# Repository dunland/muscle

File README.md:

## folder structure

**[>>FIND THE PROJECT MANUAL HERE<<](Doc/SUPER_MUSCLE_MANUAL-0.2.0.pdf)**

```
project
└───Code
│       code folder. contains subfolders 
│	└───teensy
│	│	holding the main code
│	└───debug
│	│	for Arduino-sketches used to evaluate the contact mic sensitivities
│	└───processing
│	│	with an exemplary sketch for the real-time generation of visuals
│	└───python
│		with a script supporting the calibration process graphically
└───Doc
│       Documentation folder with images and progress logs and other media files
└───hardware
│	CAD and ECAD files
└───literature
│	some interesting material on using piezo microphones, interrupts on teensy, etc
└───logs
│	this folder holds logs that are recorded from contact microphone streams
│	while playing the instruments
└───misc
	miscellaneous.
```

## project management

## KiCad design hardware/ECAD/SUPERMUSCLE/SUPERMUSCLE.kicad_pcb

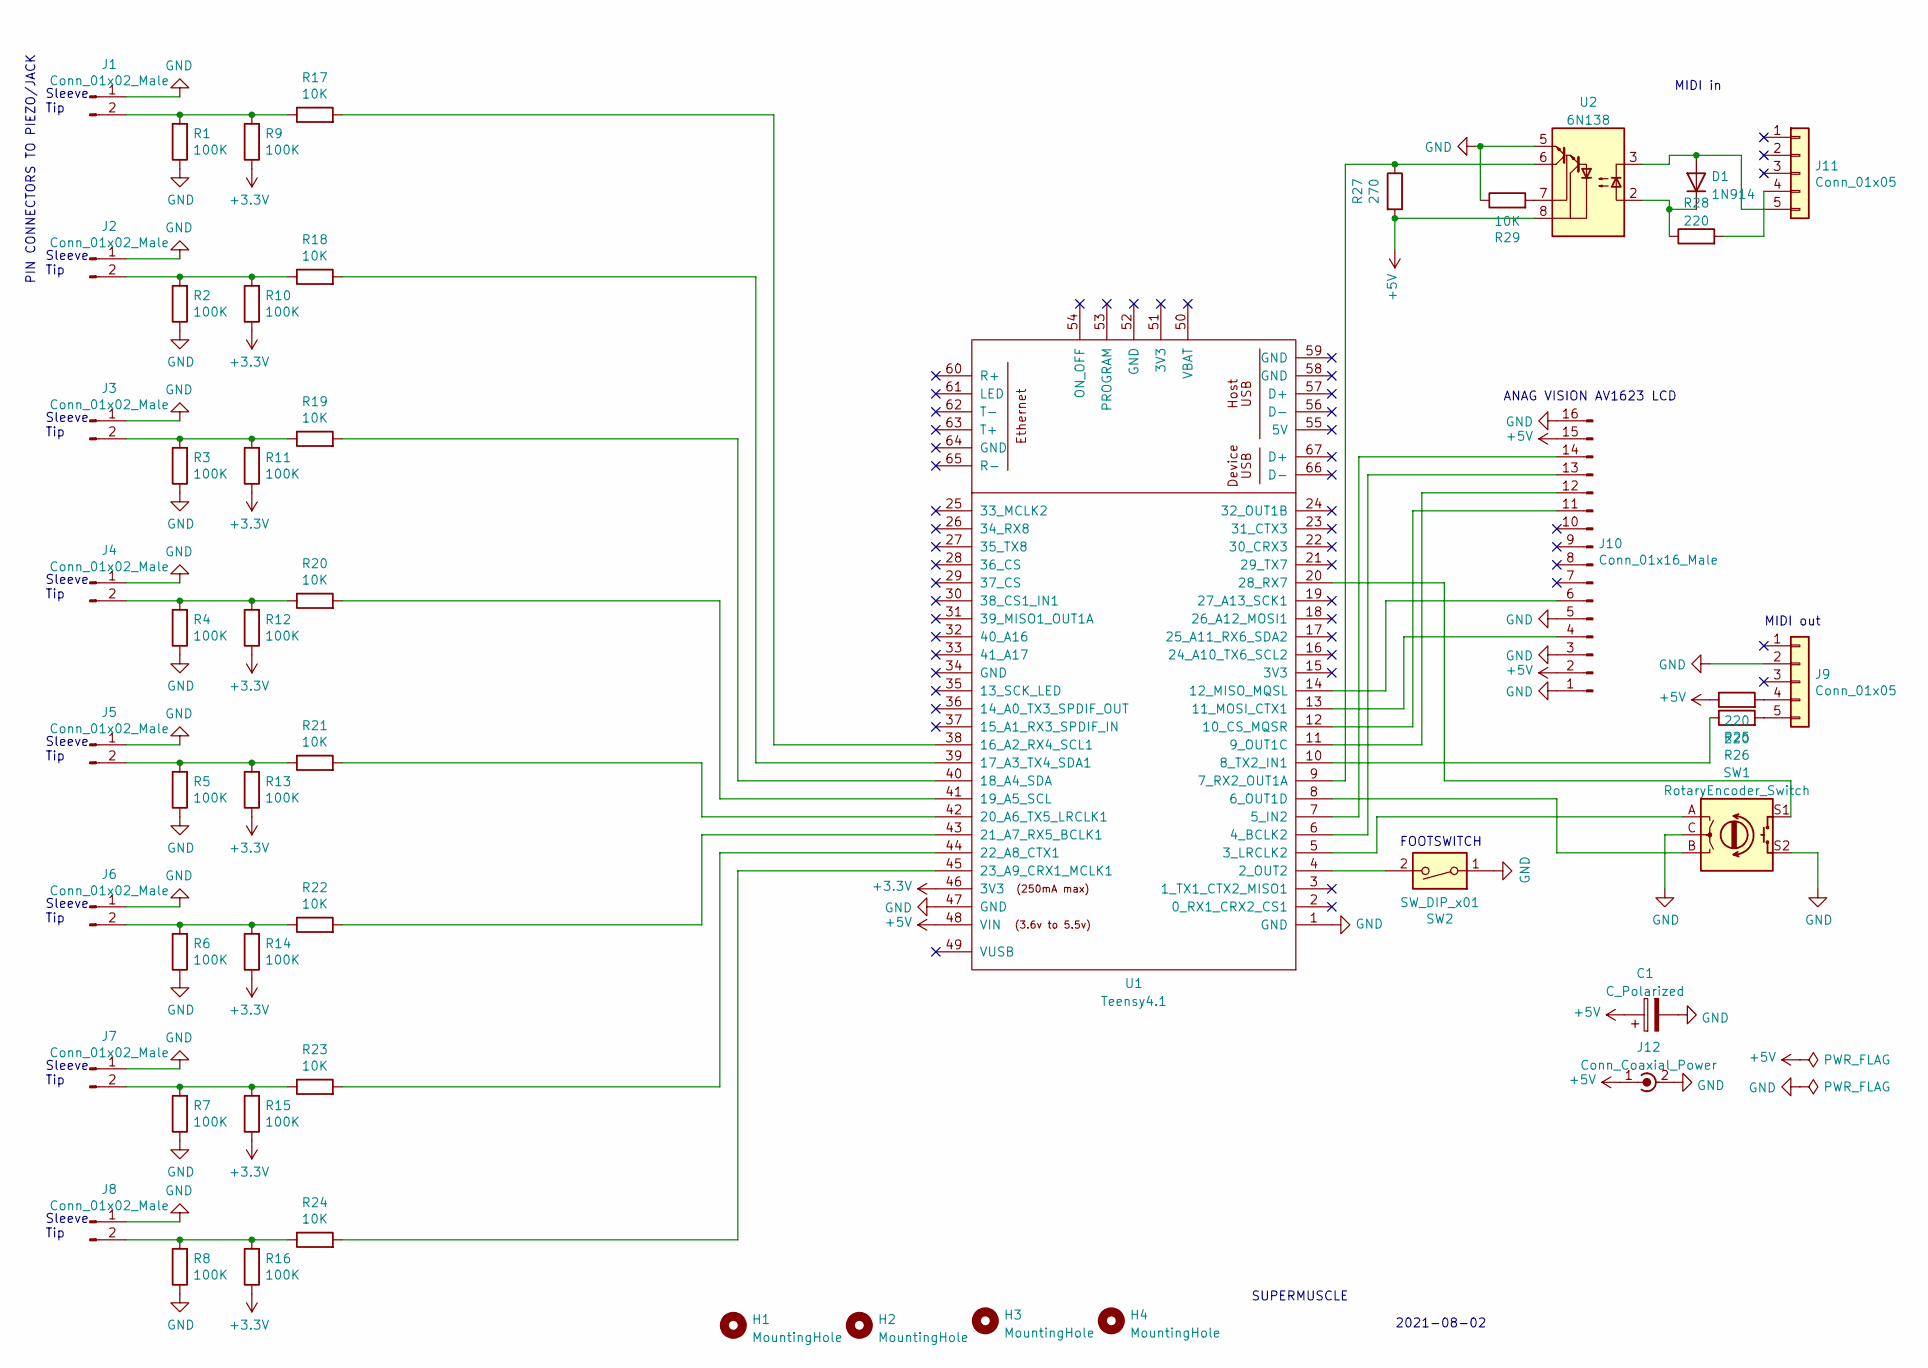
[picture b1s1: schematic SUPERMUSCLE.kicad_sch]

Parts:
C1: C_Polarized; CP_Radial_D10.0mm_P5.00mm
D1: 1N914; D_DO-35_SOD27_P7.62mm_Horizontal
H1, H2, H3, H4: MountingHole; MountingHole_4mm
J1, J2, J3, J4, J5, J6, J7, J8: Conn_01x02_Male; SolderWire-0.25sqmm_1x02_P4.2mm_D0.65mm_OD1.7mm
J9: Conn_01x05; 3pin_WirePads_MIDI_output
J10: Conn_01x16_Male; 14pin_WirePads_for_AnagVision_AV1623LCD
J11: Conn_01x05; 3pin_WirePads_MIDI_input
J12: Conn_Coaxial_Power; SolderWire-0.25sqmm_1x02_P4.2mm_D0.65mm_OD1.7mm
R1, R2, R3, R4, R5, R6, R7, R8, R9, R10, R11, R12, R13, R14, R15, R16: 100K; R_Axial_DIN0204_L3.6mm_D1.6mm_P5.08mm_Horizontal
R17, R18, R19, R20, R21, R22, R23, R24, R29: 10K; R_Axial_DIN0204_L3.6mm_D1.6mm_P5.08mm_Horizontal
R25, R26, R28: 220; R_Axial_DIN0204_L3.6mm_D1.6mm_P5.08mm_Horizontal
R27: 270; R_Axial_DIN0204_L3.6mm_D1.6mm_P5.08mm_Horizontal
SW1: RotaryEncoder_Switch; 5pin_WirePads_RotaryEncoder
SW2: SW_DIP_x01; SolderWire-0.25sqmm_1x02_P4.2mm_D0.65mm_OD1.7mm
U1: Teensy4.1; DIP-48_W15.24mm_Socket_LongPads
U2: 6N138; DIP-8_W7.62mm_Socket_LongPads

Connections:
+3V3: R9.1, R10.1, R11.1, R12.1, R13.1, R14.1, R15.1, R16.1, U1.46 (3V3)
+5V: C1.1, J10.2, J10.15, J12.1 (In), R25.1, R27.2, U1.48 (VIN), U2.8 (VCC)
GND: C1.2, J1.1, J2.1, J3.1, J4.1, J5.1, J6.1, J7.1, J8.1, J9.2, J10.1, J10.3, J10.5, J10.16, J12.2 (Ext), R1.1, R2.1, R3.1, R4.1, R5.1, R6.1, R7.1, R8.1, R29.1, SW1.C, SW1.S2, SW2.1, U1.1 (GND), U1.47 (GND), U2.5 (GND)
unnamed: D1.1 (K), R28.1, U2.2 (C1)
unnamed: D1.2 (A), J11.5, U2.3 (C2)
unnamed: J1.2, R1.2, R9.2, R17.1
unnamed: J2.2, R2.2, R10.2, R18.1
unnamed: J3.2, R3.2, R11.2, R19.1
unnamed: J4.2, R4.2, R12.2, R20.1
unnamed: J5.2, R5.2, R13.2, R21.1
unnamed: J6.2, R6.2, R14.2, R22.1
unnamed: J7.2, R7.2, R15.2, R23.1
unnamed: J8.2, R8.2, R16.2, R24.1
unnamed: J9.4, R25.2
unnamed: J9.5, R26.2
unnamed: J10.4, U1.13 (11_MOSI_CTX1)
unnamed: J10.6, U1.14 (12_MISO_MQSL)
unnamed: J10.11, U1.12 (10_CS_MQSR)
unnamed: J10.12, U1.11 (9_OUT1C)
unnamed: J10.13, U1.6 (4_BCLK2)
unnamed: J10.14, U1.7 (5_IN2)
unnamed: J11.4, R28.2
unnamed: R17.2, U1.38 (16_A2_RX4_SCL1)
unnamed: R18.2, U1.39 (17_A3_TX4_SDA1)
unnamed: R19.2, U1.40 (18_A4_SDA)
unnamed: R20.2, U1.41 (19_A5_SCL)
unnamed: R21.2, U1.42 (20_A6_TX5_LRCLK1)
unnamed: R22.2, U1.43 (21_A7_RX5_BCLK1)
unnamed: R23.2, U1.44 (22_A8_CTX1)
unnamed: R24.2, U1.45 (23_A9_CRX1_MCLK1)
unnamed: R26.1, U1.10 (8_TX2_IN1)
unnamed: R27.1, U1.9 (7_RX2_OUT1A), U2.6 (VO2)
unnamed: SW1.A, U1.5 (3_LRCLK2)
unnamed: SW1.B, U1.8 (6_OUT1D)
unnamed: SW1.S1, U1.20 (28_RX7)
unnamed: SW2.2, U1.4 (2_OUT2)
unnamed: R29.2, U2.7 (VO1)

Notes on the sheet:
Sleeve Tip
MIDI out
SUPERMUSCLE
FOOTSWITCH
PIN CONNECTORS TO PIEZO/JACK
MIDI in
2021-08-02
ANAG VISION AV1623 LCD

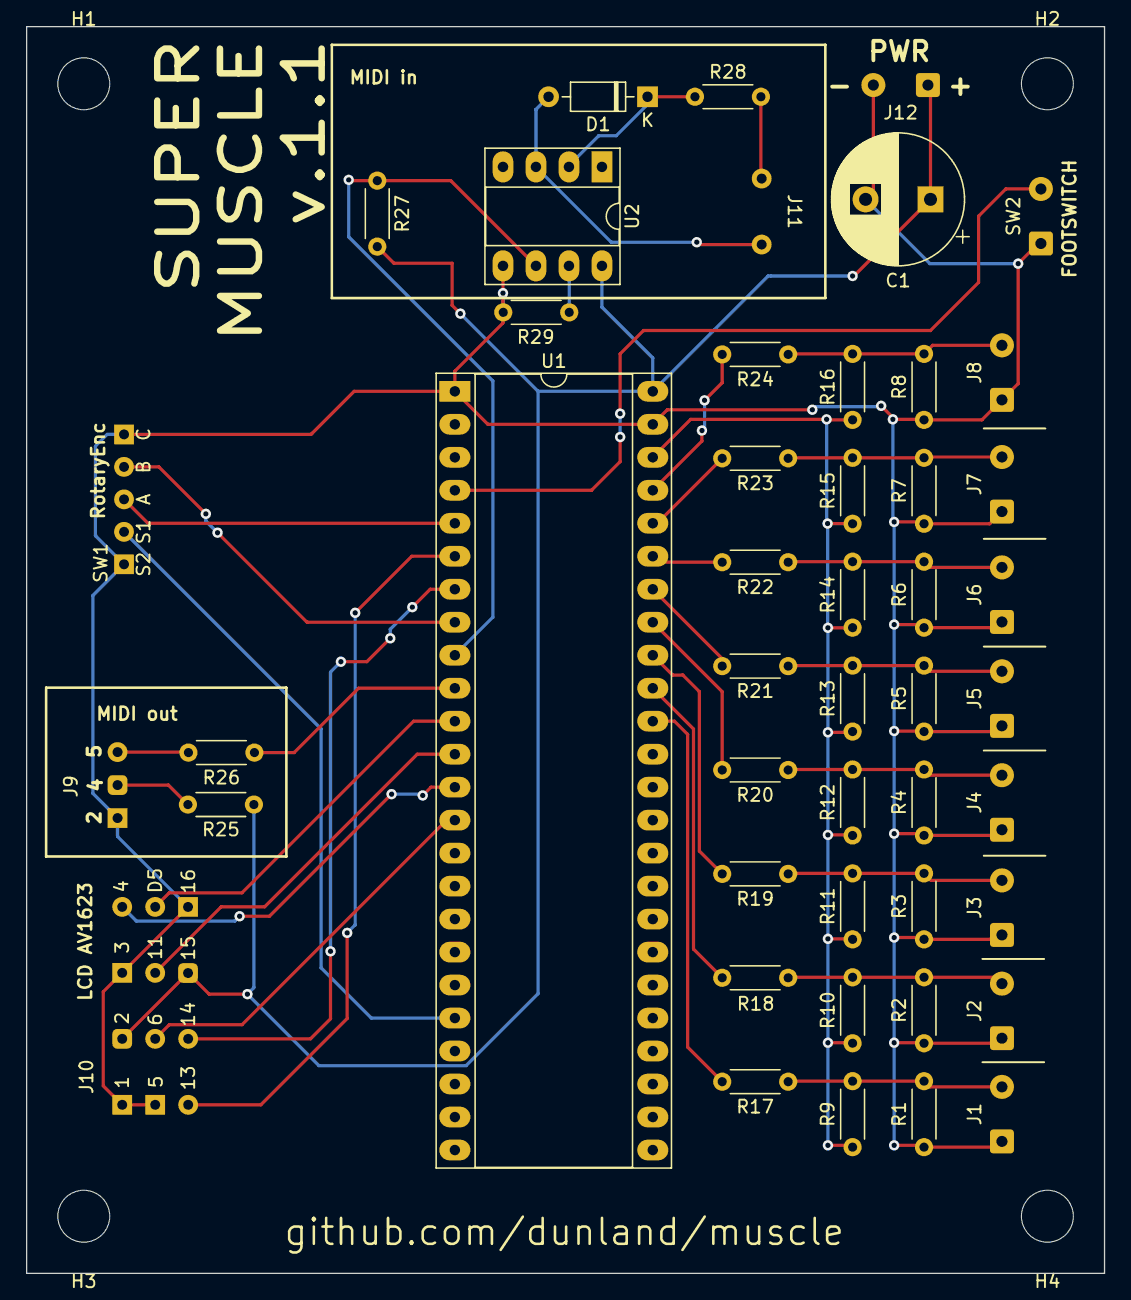
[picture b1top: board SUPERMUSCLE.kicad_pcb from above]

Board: 2 copper layers, 83.0 x 96.0 mm, 51 parts (0 on the bottom side), 37 nets.

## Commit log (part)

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2019-11-14 upload
2020-05-15 muscle/piezoDrums initial commit
2020-05-15 new order
2020-05-15 old stuff (re)moved
2020-05-18 recording tests 2020-05-16
2020-05-18 playback of one soundfile on SPRESENSE
2020-05-26 controlled Audio
2020-05-26 neu sortiert
2020-05-26 processing
2020-05-26 remove muscle
2020-05-26 restore some files
2020-05-26 single thread working
2020-05-31 Arduino tap tempo
2020-06-04 MIDI tap tempo sync working
2020-06-04 multifunctional midi setup #1
2020-06-07 sending MidiNotes works
2020-06-07 global clock vorbereitet
2020-06-07 misc
2020-06-23 anachronism sketches
2020-06-23 timeline update
2020-06-30 going over to using teensy
2020-07-01 2020-07-01
2020-07-06 pin readings speed assesment
2020-07-06 progress 2020-07-07
2020-07-06 Doc added
2020-07-10 sensor logging procedure #01
2020-07-10 tidied a bit
2020-07-14 first implementations of major code
2020-07-21 instrument symbol logger
2020-07-21 time-based logging works! prints at each beat-subdivision
2020-07-21 complete logging-playalong
2020-07-22 instruments sensitivity documentation
2020-07-29 Tap Tempo and Debug Master Code
2020-07-30 Pd moved and default processing sketch fixed
2020-08-27 define instrument names, calibration value handling
2020-08-28 responsive calibration and tap tempo fixes
2020-08-28 eighthBeatPrecision + InstrumentPrintLog columns fix
2020-08-28 2020-08-28 progress
2020-08-31 MIDI Clock fix?
2020-08-31 footswitch for pinMode 3 (record and replay via MIDI)
2020-08-31 MIDI Clock fix!
2020-08-31 footswitch PULLUP
2020-08-31 reset initialPinActions after footswitch release
2020-08-31 introducing multiple tabs; serious code formatting
2020-09-04 INTRODUCING MIDI "SWELL" EFFECT
2020-09-04 README.md with progress overview added.
2020-09-04 SWELL + MIDI Control Change
2020-09-08 SWELL USED FOR MIDI CC ONLY -- stable!
2020-09-08 SWELL: non-quantized version (bad version)
2020-09-09 removed Master_Thesis from here
2020-09-11 footswitch mode for SWELL & serial to processing
2020-09-22 testing Tsunami setup
2020-09-23 some beautifications
2020-09-29 Tsunami implementation + speaker drum head
2020-10-02 tsunami beat-linked playback working
2020-10-09 16th-note topography for MIDI playback
2020-10-09 beautifications 2020-10-09
2020-10-12 function for smoothing arrays
2020-10-16 restore point setInstrumentPrintString
2020-10-18 restore point MIDI
2020-10-18 restore point pinAction 3 (toggleRhythmSlot)
2020-10-18 restore point tapTempo + masterClock
2020-10-19 restore point perform pinAction 2 & 3
2020-10-19 restore point calculateNoiseFloor
2020-10-19 restore point Hardware+footswitch
2020-10-19 restore point stroke detection
2020-10-20 restore point print_to_console
2020-10-20 restore point smoothen_dataArray
2020-10-20 restore point pinAction 8 (TopographyLog)
2020-10-20 restore point vibration motor
2020-10-21 moved Pd
2020-10-21 uploadable
2020-10-21 topographies are vectors
2020-10-21 derive_topography function
2020-10-21 before merge
2020-10-21 Merge pull request #4 from dunland/platformio
    Platformio
2020-10-22 finally... merge complete
2020-10-23 Serial print using global function
2020-10-23 pass millis to processing
2020-11-03 trying to implement a beat regularity detection...
2020-11-03 kinda random score elements
2020-11-05 direct drum feedback on CC effects sound much nicer.
2020-11-06 dynamic instruments list
2020-11-06 trying to remove Globals::numInputs
2020-11-06 drop tom1
2020-11-07 output_string as part of Instrument class
2020-11-07 make tapTempo half-time if BPM>180 (eighth notes)
2020-11-07 alternative instruments iterator
2020-11-07 get dynamic instruments vector to work!
2020-11-07 MIDI channels für VOLCA und mKORG
2020-11-08 TOPOGRAPHY is a class now
2020-11-09 add bass note at score.step = 2
2020-11-11 new pins and beautifications
2020-11-11 starting to write a whole song in score
2020-11-12 some score advances
2020-11-12 no Effects class and static Score class
2020-11-12 score step 4
2020-11-13 skip score step 3
2020-11-16 change bass note properly + more score events
2020-11-18 create Synthesizer class
2020-11-18 replace all MIDI.sends by Synthesizer functions
2020-11-19 processing read JSON
2020-11-19 first Visuals
2020-11-19 beautifications
2020-11-20 trying to fix beat_regularity check
2020-11-20 json compiler
2020-11-21 visuals + arduinoJSON
2020-11-24 use FX2D renderer
2020-11-27 better JSON Comm + new score
2020-11-28 fixed topo parsing + stroke transmission
2020-11-28 comment and beautifications
2020-11-28 instrument stroke transmission via wasHit flag via JSON
2020-11-29 Random_CC_Effect
2020-12-01 topography functions not Global functions anymore
2020-12-03 release 0.2.0
2020-12-03 updated project overview
2020-12-04 additions to v0.2.0
2020-12-04 Vorführung Stasi
2020-12-06 Score-Song wie Bunkervideo mit Stasi 2020-12-06
2021-03-01 Rhythmics class walks stepwise through beat to execute beat-linked functions
2021-03-01 Score as nonstatic class jeder score soll einen eigenen Song darstellen..
2021-03-01 public Drumset class
2021-03-01 Reflex_and_PlayMidi-Effect + "EXPERIMENTAL" footswitch-/score-mode
2021-03-08 Rotary Encoder and LCD in Hardware class
2021-03-27 global active_score
2021-03-27 increase step using push encoder
2021-03-27 Songs.cpp erstellt
2021-03-27 elektrosmoff song step 2 break fix
2021-04-03 fixing experimental song + Serial message when hit
2021-04-07 P5 visuals
2021-04-11 elektrosmoff fix, introducing settings.h
2021-04-23 enum FootswitchMode
2021-05-10 display toggling: score / CC_mode
2021-05-11 show score title AND CCs when num of CC instr < 4
2021-05-17 global Drumset::instruments + reset to Monitor resetting instruments to Monitor when leaving a Song
2021-06-15 calibration branch
2021-06-17 good progress.. zwischenspeichern
2021-07-10 Sattelstein Score
2021-07-10 Instrument Effects is own cpp file now
2021-07-10 link tapTempo to score-specific range
2021-07-11 leave calibration mode when holding pushButton
2021-07-15 rename Serial.h→JSON.h, read from SD
2021-07-24 dd200 communication working
2021-07-24 Global Synthesizers
2021-07-26 DD200 experiments; automatic mKorg Voice Selection
2021-07-27 instruments reset and MIDI program Change
2021-07-30 Auftritt im TUNNEL
2021-08-02 rename teensy>teensy3.2
2021-08-02 separate Song files
2021-11-24 whammyMountains - test code
2021-11-28 whammy control works!
2021-12-06 hutschnur
2022-01-11 tapTempo fix
2022-01-15 dd200_timeControl
2022-01-15 dd200_timeControl FIX
2022-01-15 dd200_timeControl w/ crash trigger + MIDI Clock
2022-01-20 do not use topography class
2022-01-20 neuer_commit
2022-01-25 Notes.h
2022-01-27 control volca
2022-02-07 more sensitive bass and snare
2022-02-07 tapTempo differentiation between 4th and 8th
2022-02-10 update control_dd200
2022-02-10 update controls dd200: toggleEffects
2022-02-21 monitoring: stop active notes
2022-03-08 fusion visuals control
2022-05-10 Sandbox Code for Serial Parsing
2022-05-10 ECAD upload
2022-05-10 NanoKontrol input receive - TODO: allocate variables to addresses (using pointers?) - Tsunami was commented out, because it uses AltSoftSerial, which is not compatible with teensy4.1 (which I used fo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
2022-05-16 data allocation test
2022-05-16 allocate parsed values to variables - paramsToChange[3] always changes with value of paramsToChange[2].. TODO: fix this!
2022-05-17 fix switch escape
2022-05-17 print human readable CC_Types
2022-05-17 microKORG controllable
2022-05-17 proper midi device allocation
2022-05-19 dd200-midi-to-bpm
2022-05-19 MIDI control change test code
2022-05-19 fix NanoKontrol printToLCD
2022-05-19 NanoKontrol Song / Sattelstein
2022-05-20 global bool whether to dis-/enable midi clock send
2022-05-20 synthesizers dynamic midi value storage
2022-05-20 broken code? does not send midi to dd200
2022-05-23 concert at stasi's
2022-06-16 fix snare's midi channel for dd200
2022-06-20 .ist dd200 mod CC
2022-06-20 rename CC Types
2022-07-07 add LFO 1/2
2022-07-12 some new songs + merge w/ W530
2022-07-12 whammy midi programs hutschnur, pogo, roeskur
2022-07-22 rename Score->Song, add some songs
2022-07-22 rename active_score->active_song
2022-07-27 update tom sensibility
2022-08-12 randomvoices mit dd200 control
2022-08-12 update for new piezos
2022-08-13 preparing forsthaus
2022-08-15 rename Score.cpp Song.cpp
2022-09-22 compiles without Errors
2022-09-24 Hardware updates
2022-09-24 correct pushbutton pins for teensy4.1
2022-09-24 trying to fix calibration mode pushbutton handling
2022-09-30 sensitivity for SUPERMUSCLE 0.3
2022-11-25 organize songs ferdinandPiech, queen, donnerwetter
2022-11-29 WIP: trying to pass callback function
2022-11-29 setlist fürs konzert
2023-03-29 updated hardware
2023-03-29 pd updates and serial communication
2023-03-31 add kaosspad
2023-03-31 removing some errors
2023-04-06 initialize randomSelect
2023-04-06 progress
2023-04-06 deactivate touchpad after alhambra
2023-04-07 no more errors!
2023-04-07 organize new songs, create b_11
2023-04-07 b_11 and b_36
2023-04-07 automatically deactivate setup_song
2023-04-10 updated synth songs
2023-04-10 some marks
2023-04-10 toggle display to show instruments midi channel
2023-04-13 work in progress ... missing: note activation for some songs, Arp HOLD, CC-effects for others..
2023-04-13 WIP: trying to set b_63, but setup() not called
2023-04-17 fix compile errors, rename "host" and "besen"
2023-04-20 setlist
2023-04-20 intro song
2023-04-20 last commit before concert
2023-04-22 update songlist
2023-07-17 Devtools + Globals::get_song + Song::random_select
2023-07-17 song.name in constructor, randomSelect works!
2023-07-17 trying to fix randomSelect hangUps, rename instr.midi
2023-07-18 UNTESTED: lcd song information + autoscroll
2023-07-19 do not scroll display (yet...)
2023-07-19 b_27 info
2023-07-19 randomSelect song updates
2023-07-27 volca permanently triggered, A72 intro, song fixes
2023-07-29 update songlist for 30 min set
2023-08-01 setup state of active song initially true + A72 dynamics update
2023-08-21 A72 dynamics
2023-09-01 added notes to songs
2023-09-05 python script to trigger hydra visuals
2023-09-05 MIDI only needed in Hardware file
2023-09-21 hardware update
2023-09-22 pcb + code annotations
2023-09-22 extinguish errors after merge
2023-09-27 remove old teensy4.1 folder
2023-09-27 Calibration mode menu + SD handling
2023-10-04 rename Standtom, debug SD, switch Encoder Pins
2023-11-08 songlist + instruments
2023-11-08 fixed instrument pins + presets for whammy+dd200
2023-11-23 spezifische song-timing-einstellungen
2023-11-24 song sturmUndDrang, Devtools::serial_comm, rename dd200 delayFeedback
2023-11-29 overwrite SD data, rename dd200feedback
2023-11-29 TO TEST: trigger instr only once per 32nd
2023-11-29 TEST ARPONOFF FUNCTION + sensititvity update
2023-12-12 control whammy expression lvl
2024-01-04 fix dd200 cc_types
2024-01-22 changes compile successfully
2024-01-29 eliminate errors. works on test device now
2024-01-29 upgrade CC display + setup sturmUndDrang synths
2024-01-30 volca Keys CC numbers
2024-01-30 update sturmUndDrang trigger FX
2024-01-30 sturmUndDrang: Zerhechsel works!
2024-02-29 triathlon neuer song
2024-02-29 triathlon ablauf
2024-04-11 sloJam, tapTempo, MIDI fixes
2024-04-15 using callback functions for footswitch as object
2024-04-16 rename proceedToNextSong
2024-05-02 sloJam control mKORG
2024-05-30 sloJam 65BPM
2024-08-26 beautifications + tracklist für september 2024
2024-09-26 rename protected variables
2024-09-26 calibration debug prints
2025-02-16 enhance trigger precision for nosferatu
2025-05-19 konzert dirty dancing 22.02.25
    - reihenfolge der songs
    - songs umbenannt
    - warte anfangs auf USB
    - set midi effect to Monitor on failure
    - use drum trigger effects only in "Running" mode
    - randomVoices updates
2025-05-25 fix randomVoices hangUp error
    - MIDI_TARGETs have preinitialized notes, active_note and cc_type
    - addMidiTarget function overload with int cc_type
    - midiTargets in randomVoices start off with random CC_type
    - all instrument start off with Monitor effect
    - shuffle_cc function can set CC from random int more easily
    - PlayMidi effect adds random notes if not initialized
2025-06-13 fix multi-line lcd output at changeCC
2025-06-23 introducing tonale modi for randomVoices
2025-09-27 randomVoice: play continuous note
2025-09-27 beautifications + stabilizations
2025-09-28 hold button -> enter calibration mode
